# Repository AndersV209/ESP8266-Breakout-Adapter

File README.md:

###ESP-07 & ESP-12 Breakout Adapter

####Version 1.0 - LM1117 - AndersV209 custom (untested)
Used LDO: AMS1117
Vin=4.8-15V, Dropout=1.2V, Iq=5mA(-10mA)

####Version 1.1 - LM1117 (tested, works great)
Used LDO: LM1117
Vin=4.8-15V, Dropout=1.2V, Iq=5mA(-10mA)

oshpark: https://oshpark.com/shared_projects/9CsYq2PY

####Version 2.0A - AS1363 (untested, in production)
Used LDO: AS1363
Vin=3.5-5.5V, Dropout=150mV(-320mV), Iq=40µA

oshpark: https://oshpark.com/shared_projects/2IkxaFPm

####Version 2.0B - SPX3819 (untested, in production)
Used LDO: SPX3819 
Vin=3.7-16V, Dropout=340mV(-550mV), Iq=90µA

oshpark: https://oshpark.com/shared_projects/jsl8ZcFp

####Version 3.0A - AS1363 - Mini (untested)
Used LDO: AS1363
Vin=3.5-5.5V, Dropout=150mV(-320mV), Iq=40µA

oshpark: https://oshpark.com/shared_projects/BgaX81QE

####Version 3.0B - SPX3819 - Mini (untested)
Used LDO: SPX3819 
Vin=3.7-16V, Dropout=340mV(-550mV), Iq=90µA

oshpark: https://oshpark.com/shared_projects/zpDg7761

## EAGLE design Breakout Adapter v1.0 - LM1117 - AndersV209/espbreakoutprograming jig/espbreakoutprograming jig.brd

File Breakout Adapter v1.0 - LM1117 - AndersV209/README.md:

CUSTOM Version by AndersV209

#ESP-12E Breakout Adapter

###Features
* 3V3 voltageregulator (LM1117/AMS1117/..)
* Breadboard compatible
* Reset Button
* Pullup restor for CH_PD

###Partlist:
**ESP8266**
* 1x - ESP12E/ESP12F

**Vreg**
* 1x - x1117-3.3 - [SOT223]

**Caps**
* 1x - 100nF - [0805]
* 2x - 10µF - [0805]

**Switches**
* 1x - Tactile Switch - [THT/SMD]

**Resistors**
* 3x - 10K - [0805]
* 1x - 0R - [0805]

**Pin Header**
* 2x - 1x13 - 2,54 mm 
* 1x - 1x6 - 2 mm 
* 2x - 1x8 - 2 mm 

###Resourcen:
* AMS1117 Datasheet - http://www.advanced-monolithic.com/pdf/ds1117.pdf
* LM1117 Datasheet - http://www.ti.com/lit/ds/symlink/lm1117-n.pdf

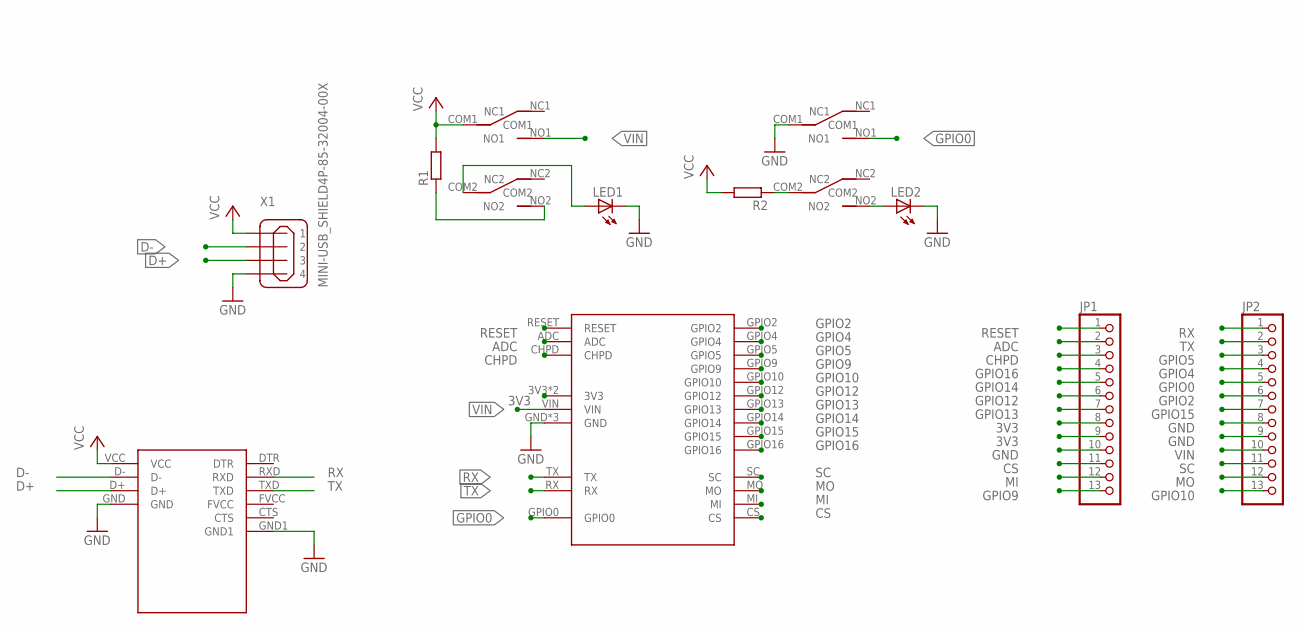
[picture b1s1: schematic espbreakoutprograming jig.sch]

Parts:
FLASH: TOGGLE_SWITCH; 7MMX7MM
JP1, JP2: PINHD-1X13; 1X13
LED1, LED2: LED5MM
POWER: TOGGLE_SWITCH; 7MMX7MM
R1, R2: R-EU_0207/10; 0207/10
U$1: USB-TTL; USB_TTL
U$2: ESP12EBREAKOUT
X1: MINI-USB_SHIELD4P-85-32004-00X; 85-32004-00X

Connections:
3V3: JP1.8, JP1.9, U$2.3V3, U$2.3V3_2 (3V3)
ADC: JP1.2, U$2.ADC
CHPD: JP1.3, U$2.CHPD
CS: JP1.11, U$2.CS
D+: U$1.D+, X1.3
D-: U$1.D-, X1.2
GND: FLASH.COM1, JP1.10, JP2.8, JP2.9, LED1.K (C), LED2.K (C), U$1.GND, U$1.GND1, U$2.GND, U$2.GND_2 (GND), U$2.GND_3 (GND), X1.4
GPIO0: FLASH.NO1, JP2.5, U$2.GPIO0
GPIO2: JP2.6, U$2.GPIO2
GPIO4: JP2.4, U$2.GPIO4
GPIO5: JP2.3, U$2.GPIO5
GPIO9: JP1.13, U$2.GPIO9
GPIO10: JP2.13, U$2.GPIO10
GPIO12: JP1.6, U$2.GPIO12
GPIO13: JP1.7, U$2.GPIO13
GPIO14: JP1.5, U$2.GPIO14
GPIO15: JP2.7, U$2.GPIO15
GPIO16: JP1.4, U$2.GPIO16
MI: JP1.12, U$2.MI
MO: JP2.12, U$2.MO
unnamed: POWER.NO2, R1.1
unnamed: LED1.A, POWER.COM2
unnamed: FLASH.COM2, R2.1
unnamed: FLASH.NO2, LED2.A
RESET: JP1.1, U$2.RESET
RX: JP2.1, U$1.RXD, U$2.TX
SC: JP2.11, U$2.SC
TX: JP2.2, U$1.TXD, U$2.RX
VCC: POWER.COM1, R1.2, R2.2, U$1.VCC, X1.1
VIN: JP2.10, POWER.NO1, U$2.VIN

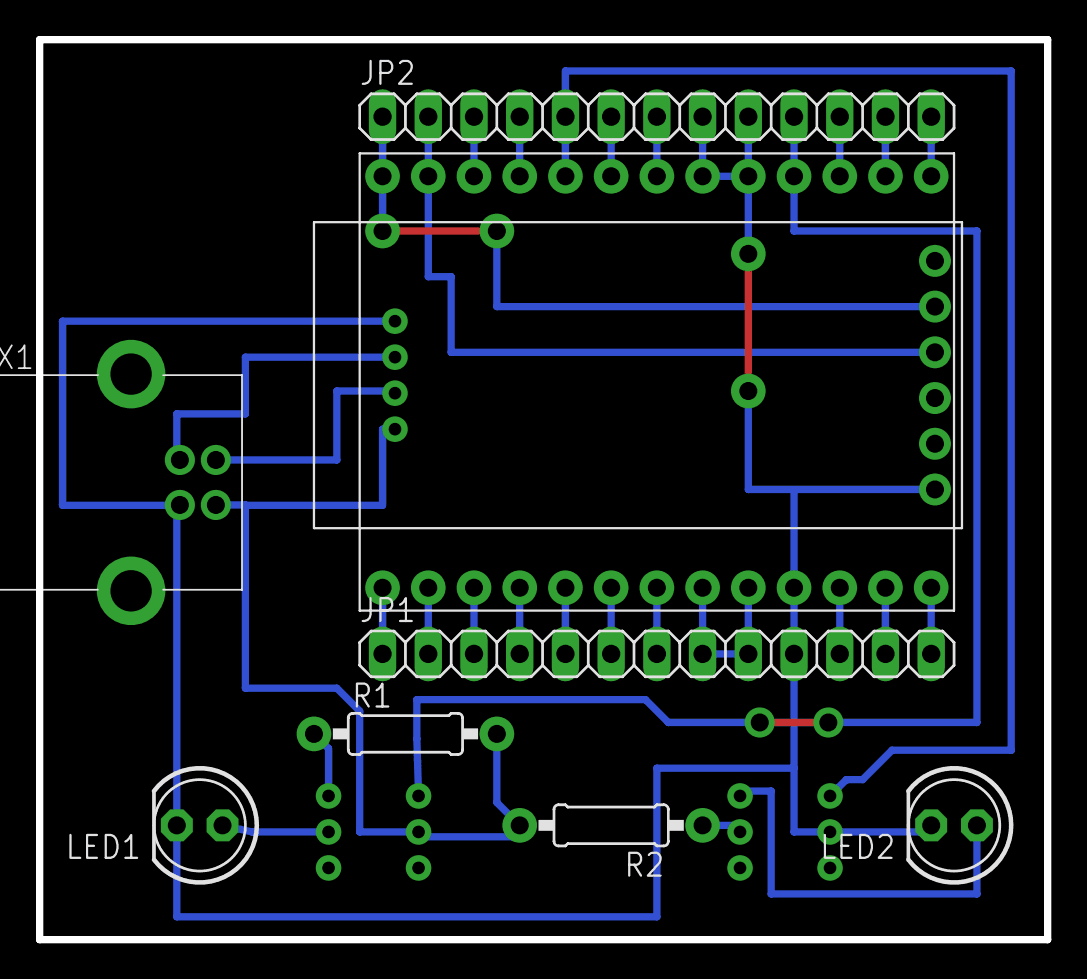
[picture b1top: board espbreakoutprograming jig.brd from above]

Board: 2 copper layers, 56.0 x 50.0 mm, 11 parts (0 on the bottom side), 30 nets.

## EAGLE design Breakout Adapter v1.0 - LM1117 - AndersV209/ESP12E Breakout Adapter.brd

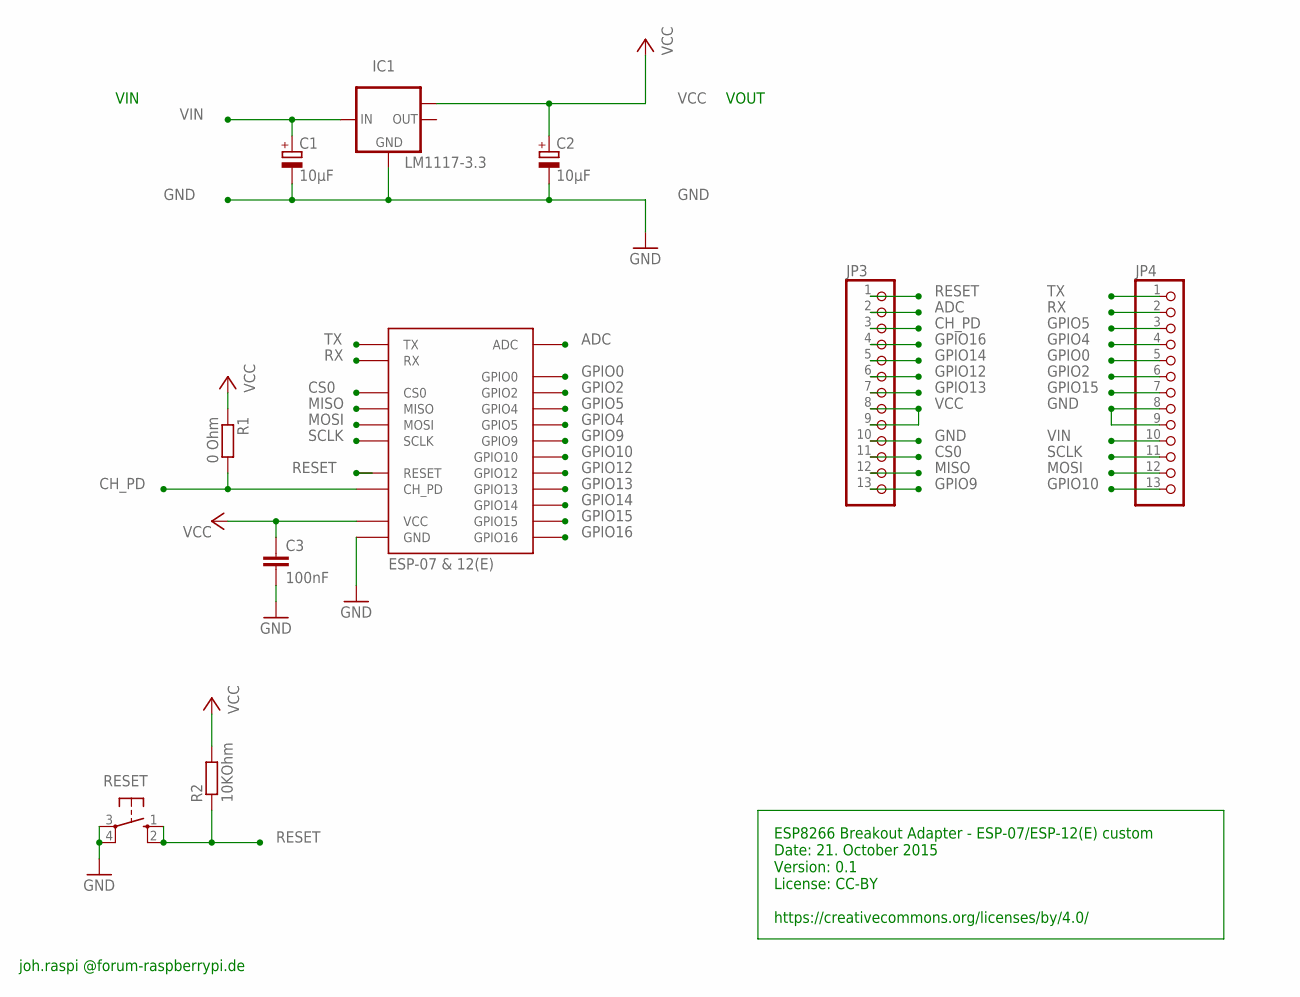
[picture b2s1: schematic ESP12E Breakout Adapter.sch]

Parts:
C1, C2: 10µF; B/3528-21W
C3: 100nF; C0805K
ESP8266: ESP-07 & 12(E); ESP-12-E
IC1: LM1117-3.3; SOT223
JP3, JP4: PINHD-1X13; 1X13
R1: 0 Ohm; R0805
R2: 10KOhm; R0805
RESET_SWITCH: RESET; B3F-10XX

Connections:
ADC: ESP8266.ADC, JP3.2
CH_PD: ESP8266.CH_PD, JP3.3, R1.2
CS0: ESP8266.CS0, JP3.11
GND: C1.-, C2.-, C3.2, ESP8266.GND, IC1.1 (GND), JP3.10, JP4.8, JP4.9, RESET_SWITCH.3, RESET_SWITCH.4 (P1); also elsewhere on the board
GPIO0: ESP8266.GPIO0, JP4.5
GPIO2: ESP8266.GPIO2, JP4.6
GPIO4: ESP8266.GPIO5, JP4.4
GPIO5: ESP8266.GPIO4, JP4.3
GPIO9: ESP8266.GPIO9, JP3.13
GPIO10: ESP8266.GPIO10, JP4.13
GPIO12: ESP8266.GPIO12, JP3.6
GPIO13: ESP8266.GPIO13, JP3.7
GPIO14: ESP8266.GPIO14, JP3.5
GPIO15: ESP8266.GPIO15, JP4.7; also elsewhere on the board
GPIO16: ESP8266.GPIO16, JP3.4
MISO: ESP8266.MISO, JP3.12
MOSI: ESP8266.MOSI, JP4.12
RESET: ESP8266.RESET, JP3.1, R2.1, RESET_SWITCH.1 (S), RESET_SWITCH.2 (S1)
RX: ESP8266.RX, JP4.2
SCLK: ESP8266.SCLK, JP4.11
TX: ESP8266.TX, JP4.1
VCC: C2.+, C3.1, ESP8266.VCC, IC1.TAB (OUT1), JP3.8, JP3.9, R1.1, R2.2
VIN: C1.+, IC1.3 (IN), JP4.10

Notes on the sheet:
VIN
VOUT
ESP8266 Breakout Adapter - ESP-07/ESP-12(E) custom Date: 21. October 2015 Version: 0.1 License: CC-BY https://creativecommons.org/licenses/by/4.0/
joh.raspi @forum-raspberrypi.de

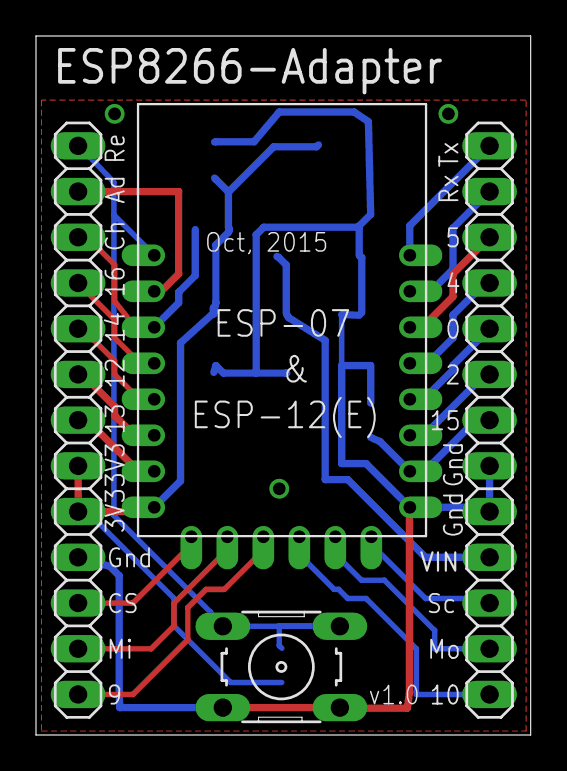
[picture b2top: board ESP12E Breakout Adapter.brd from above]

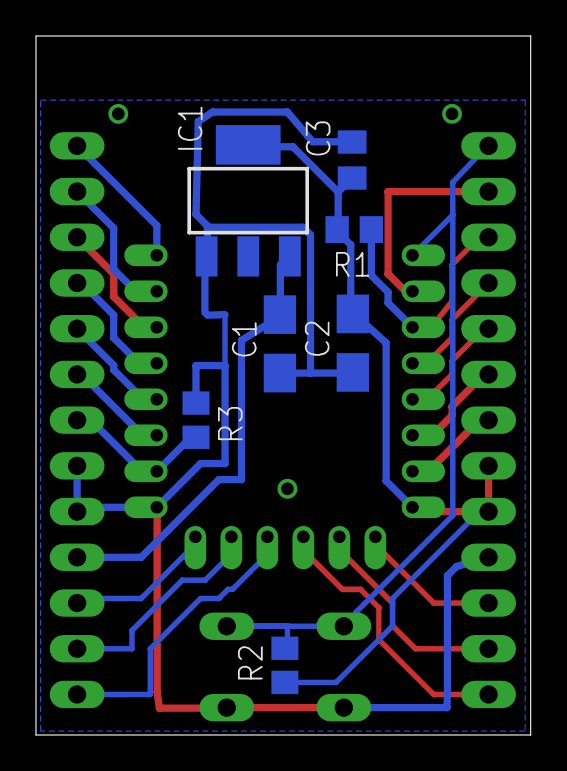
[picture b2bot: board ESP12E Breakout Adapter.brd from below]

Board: 2 copper layers, 27.5 x 38.8 mm, 11 parts (7 on the bottom side), 23 nets.

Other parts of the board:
R3: 10KOhm; R0805

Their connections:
GND: R3.1; also elsewhere on the board
GPIO15: R3.2; also elsewhere on the board

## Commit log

2015-10-21 Custum version of the ams1117 version
    My version of a ESP8266 esp12e breakout board(UNTESTED)
2015-10-21 readme.md
2015-10-21 repostiton of esp12e
2015-10-21 readme updated
2015-10-21 gerberfiles and clean up
2015-10-22 update to silkscreen
2015-10-22 Added pull down to gpio15
2015-10-22 Gerberfile update to latest board
2015-10-22 clean up
2015-10-23 gerberfiles for dirtypcb
2015-10-23 esp moved and right capacitor footprint chosen
2015-10-23 final design for first pcb order
2015-10-24 esp12e breakout programing jig eagle files
2015-11-21 update to programming jig
2015-12-06 change to text on pcb as it was in wrong layer
2015-12-06 remove temp file
2015-12-17 espbreakout eagle libary file
